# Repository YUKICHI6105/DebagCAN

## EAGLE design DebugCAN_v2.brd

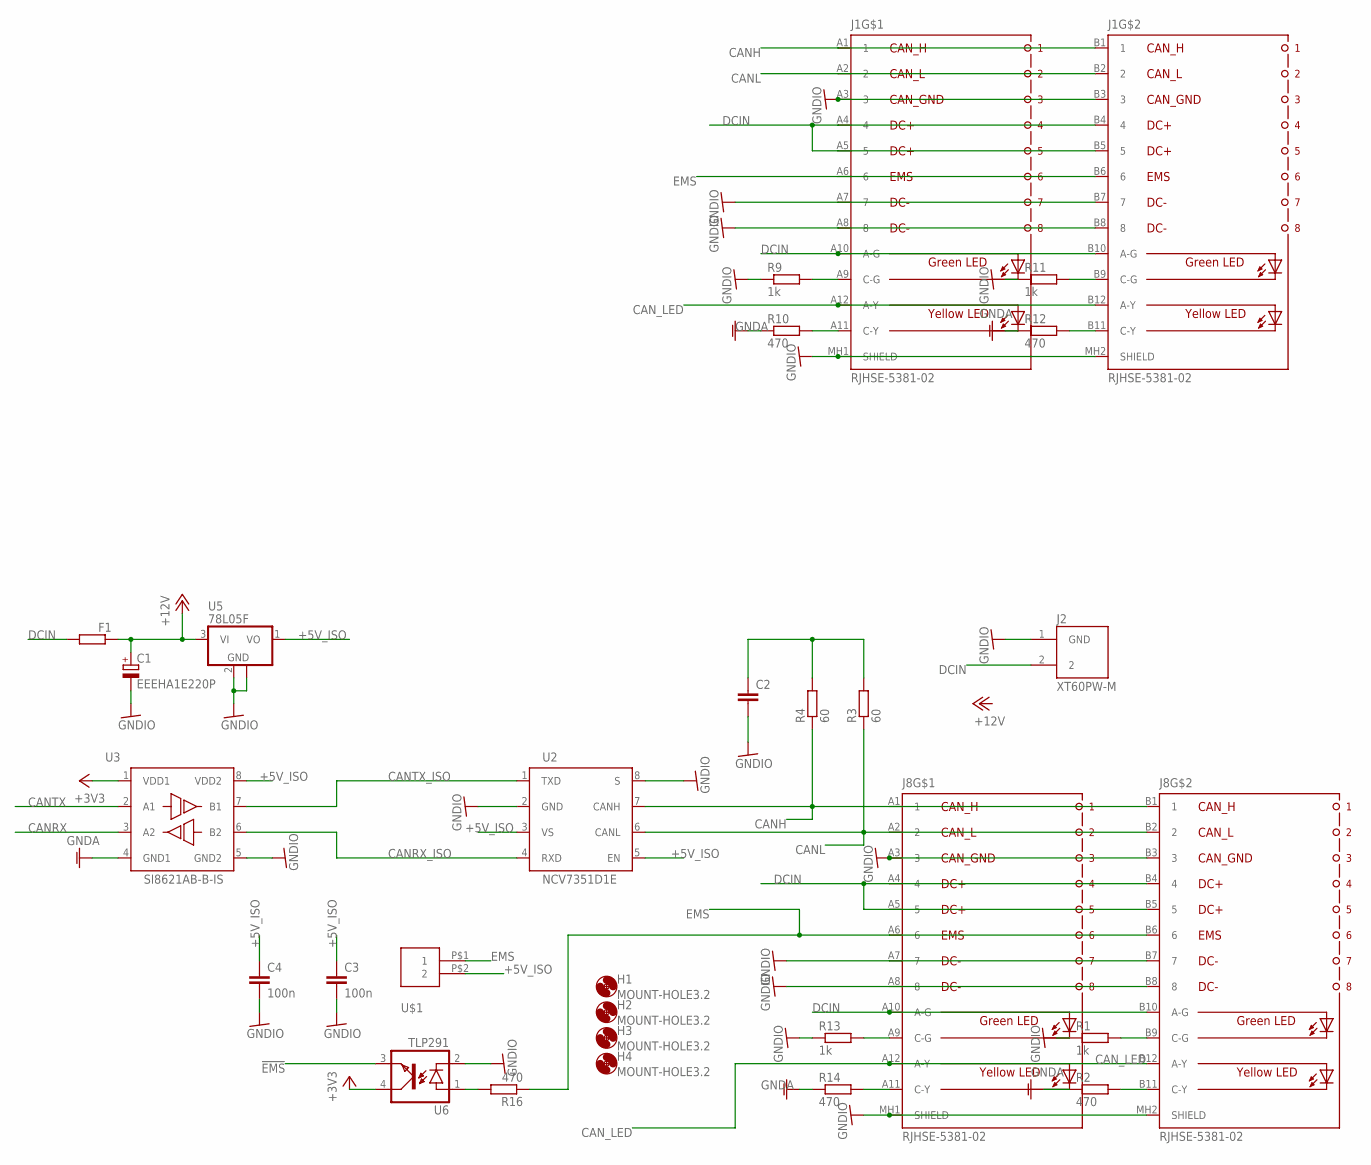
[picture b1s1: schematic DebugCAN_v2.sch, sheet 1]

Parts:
C1: EEEHA1E220P; 153CLV-0605
C2: C-EUC0603; C0603
C3, C4: 100n; C0603
F1: R-EU_R1206; R1206
H1, H2, H3, H4: MOUNT-HOLE3.2; 3,2
J1, J8: RJHSE-5381-02; RJHSE538102
J2: XT60PW-M; AMASS_XT60PW-M
R1, R9, R11, R13: 1k; R0603
R2, R10, R12, R14, R16: 470; R0603
R3, R4: 60; R0603
U2: NCV7351D1E; SO08
U3: SI8621AB-B-IS; SO08
U5: 78L05F; SOT89
U6: TLP291; MINI-FLAT-4
U$1: XH-2-STRAIGHT; CON-XH-2-STRAIGHT

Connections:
!EMS: U6.3 (EMIT); also elsewhere on the board
+3V3: U3.1 (VDD1), U6.4 (COL); also elsewhere on the board
+5V_ISO: C3.1, C4.1, U2.3 (VS), U2.5 (EN), U3.8 (VDD2), U5.1 (VO), U$1.P$2 (2)
+12V: C1.+, F1.1, U5.3 (VI)
CANH: J1.A1 (1), J1.B1 (1), J8.A1 (1), J8.B1 (1), R4.1, U2.7 (CANH)
CANL: J1.A2 (2), J1.B2 (2), J8.A2 (2), J8.B2 (2), R3.1, U2.6 (CANL)
CANRX: U3.3 (A2); also elsewhere on the board
CANRX_ISO: U2.4 (RXD), U3.6 (B2)
CANTX: U3.2 (A1); also elsewhere on the board
CANTX_ISO: U2.1 (TXD), U3.7 (B1)
CAN_LED: J1.A12 (A-Y), J1.B12 (A-Y), J8.A12 (A-Y), J8.B12 (A-Y); also elsewhere on the board
DCIN: F1.2, J1.A4 (4), J1.A5 (5), J1.A10 (A-G), J1.B4 (4), J1.B5 (5), J1.B10 (A-G), J2.2, J8.A4 (4), J8.A5 (5), J8.A10 (A-G), J8.B4 (4), J8.B5 (5), J8.B10 (A-G)
EMS: J1.A6 (6), J1.B6 (6), J8.A6 (6), J8.B6 (6), R16.1, U$1.P$1 (1)
GNDA: R2.1, R10.1, R12.1, R14.1, U3.4 (GND1); also elsewhere on the board
GNDIO: C1.-, C2.2, C3.2, C4.2, J1.A3 (3), J1.A7 (7), J1.A8 (8), J1.B3 (3), J1.B7 (7), J1.B8 (8), J1.MH1 (SHIELD), J1.MH2 (SHIELD), J2.1 (GND), J8.A3 (3), J8.A7 (7), J8.A8 (8), J8.B3 (3), J8.B7 (7), J8.B8 (8), J8.MH1 (SHIELD), J8.MH2 (SHIELD), R1.1, R9.1, R11.1, R13.1, U2.2 (GND), U2.8 (S), U3.5 (GND2), U5.2 (GND), U5.2@1 (GND), U6.2 (C)
unnamed: J1.A9 (C-G), R9.2
unnamed: J8.B9 (C-G), R1.2
unnamed: J8.B11 (C-Y), R2.2
unnamed: C2.1, R3.2, R4.2
unnamed: J1.A11 (C-Y), R10.2
unnamed: J1.B11 (C-Y), R12.2
unnamed: J1.B9 (C-G), R11.2
unnamed: J8.A11 (C-Y), R14.2
unnamed: J8.A9 (C-G), R13.2
unnamed: R16.2, U6.1 (A)

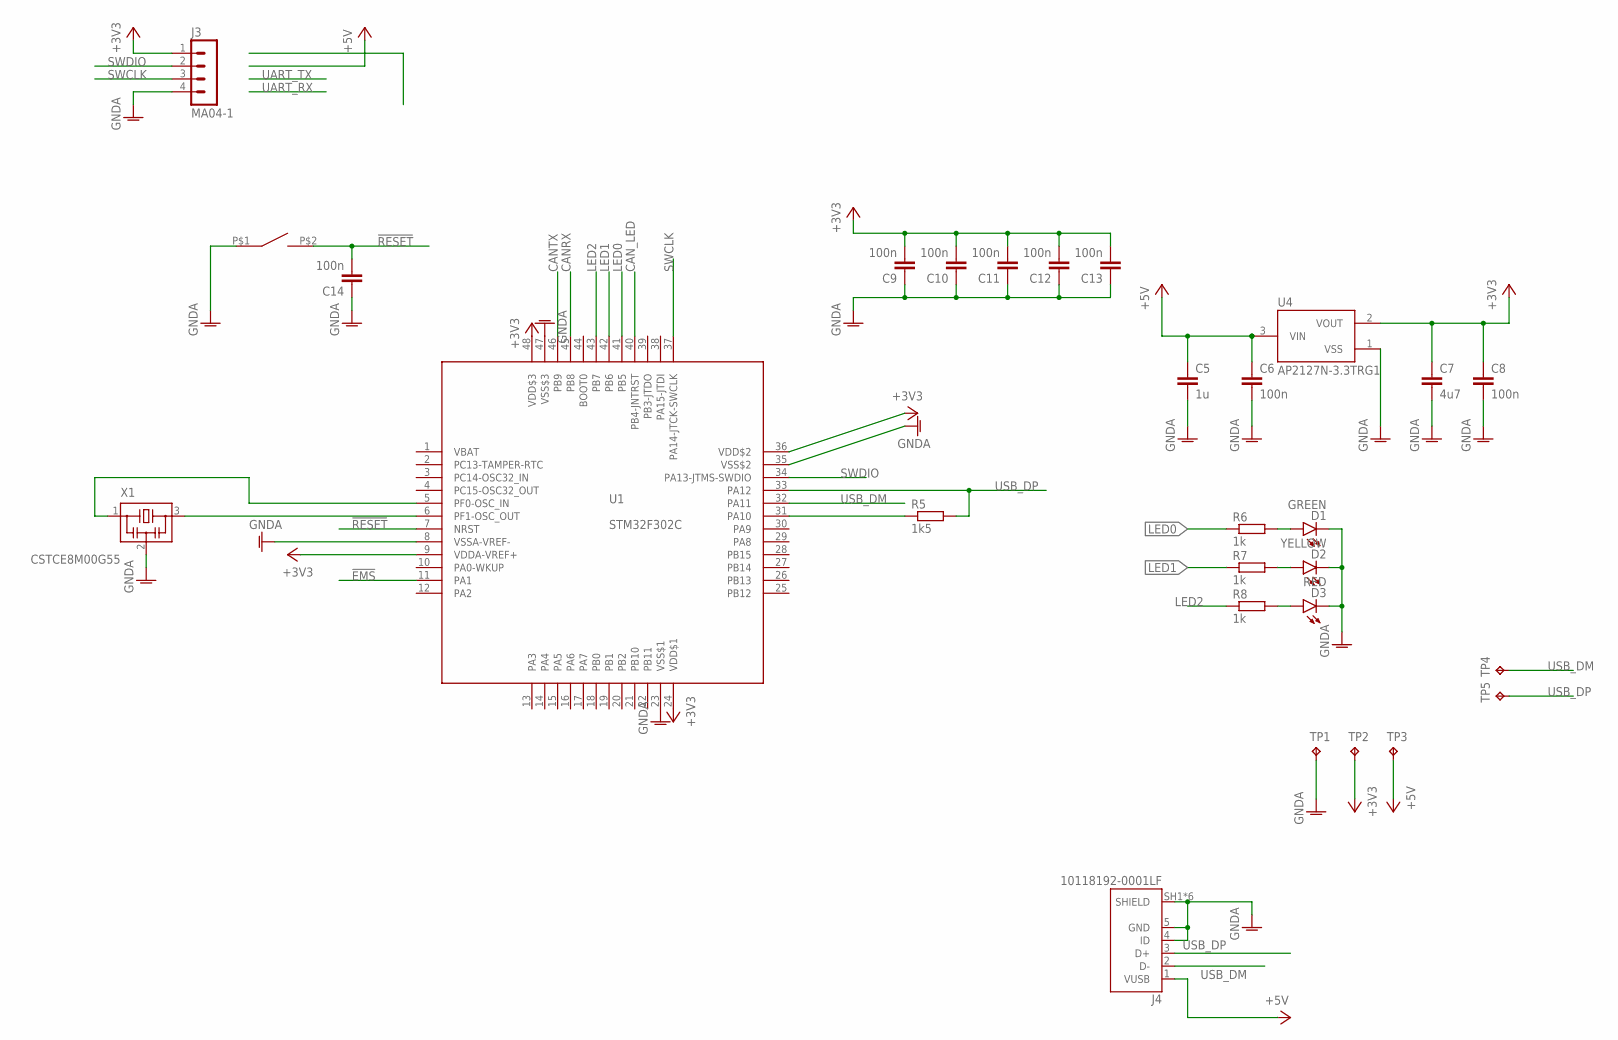
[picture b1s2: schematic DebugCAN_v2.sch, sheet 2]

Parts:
C5: 1u; C0603
C6, C8, C9, C10, C11, C12, C13, C14: 100n; C0603
C7: 4u7; C0805
D1: GREEN; CHIPLED_0805
D2: YELLOW; CHIPLED_0805
D3: RED; CHIPLED_0805
J3: MA04-1
J4: 10118192-0001LF; AMPHENOL_10118192-0001LF
R5: 1k5; R0603
R6, R7, R8: 1k; R0603
S1: SWITCH_TACTILETOP; SWITCH_TACTILE_3X6
TP1, TP2, TP3, TP4, TP5: TPB1,27; B1,27
U1: STM32F302C; LQFP48
U4: AP2127N-3.3TRG1; SOT95P240X110-3
X1: CSTCE8M00G55

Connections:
!EMS: U1.11 (PA1); also elsewhere on the board
!RESET: C14.2, S1.P$2 (2), U1.7 (NRST)
+3V3: C7.1, C8.1, C9.2, C10.2, C11.2, C12.2, C13.2, J3.1, TP2.TP, U1.9 (VDDA-VREF+), U1.24 (VDD$1), U1.36 (VDD$2), U1.48 (VDD$3), U4.2 (VOUT); also elsewhere on the board
+5V: C5.1, C6.1, J4.1 (VUSB), TP3.TP, U4.3 (VIN)
CANRX: U1.45 (PB8); also elsewhere on the board
CANTX: U1.46 (PB9); also elsewhere on the board
CAN_LED: U1.40 (PB4-JNTRST); also elsewhere on the board
GNDA: C5.2, C6.2, C7.2, C8.2, C9.1, C10.1, C11.1, C12.1, C13.1, C14.1, D1.C, D2.C, D3.C, J3.4, J4.4 (ID), J4.5 (GND), J4.SH1 (SHIELD), J4.SH2 (SHIELD), J4.SH3 (SHIELD), J4.SH4 (SHIELD), J4.SH5 (SHIELD), J4.SH6 (SHIELD), S1.P$1 (1), TP1.TP, U1.8 (VSSA-VREF-), U1.23 (VSS$1), U1.35 (VSS$2), U1.47 (VSS$3), U4.1 (VSS), X1.2; also elsewhere on the board
LED0: R6.1, U1.41 (PB5)
LED1: R7.1, U1.42 (PB6)
LED2: R8.1, U1.43 (PB7)
unnamed: D2.A, R7.2
unnamed: D1.A, R6.2
unnamed: U1.6 (PF1-OSC_OUT), X1.3
unnamed: U1.5 (PF0-OSC_IN), X1.1
unnamed: R5.1, U1.31 (PA10)
unnamed: D3.A, R8.2
SWCLK: J3.3, U1.37 (PA14-JTCK-SWCLK)
SWDIO: J3.2, U1.34 (PA13-JTMS-SWDIO)
USB_DM: J4.2 (D-), TP4.TP, U1.32 (PA11)
USB_DP: J4.3 (D+), R5.2, TP5.TP, U1.33 (PA12)

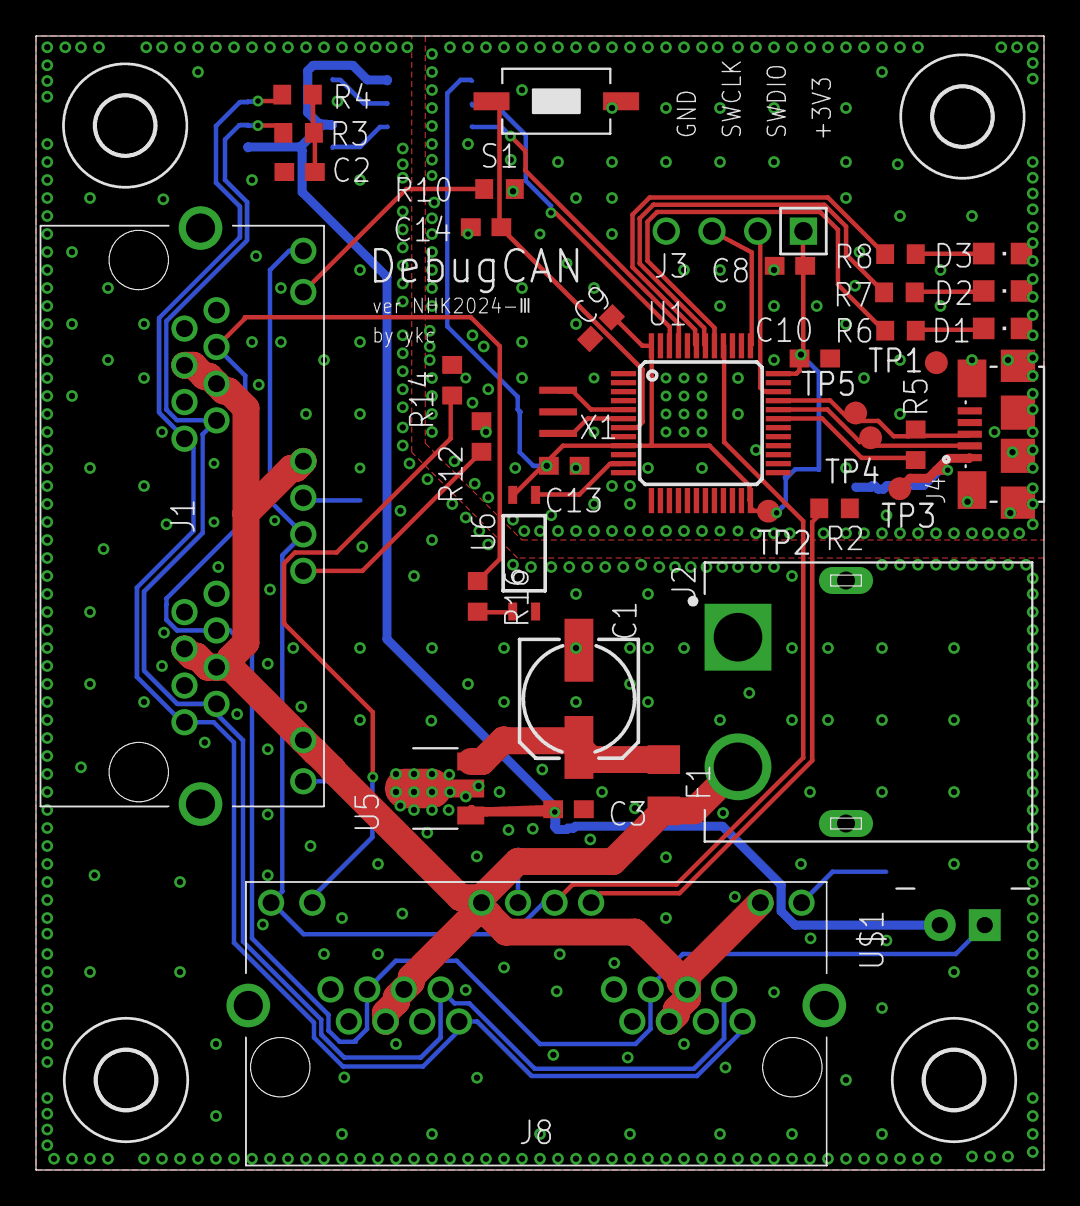
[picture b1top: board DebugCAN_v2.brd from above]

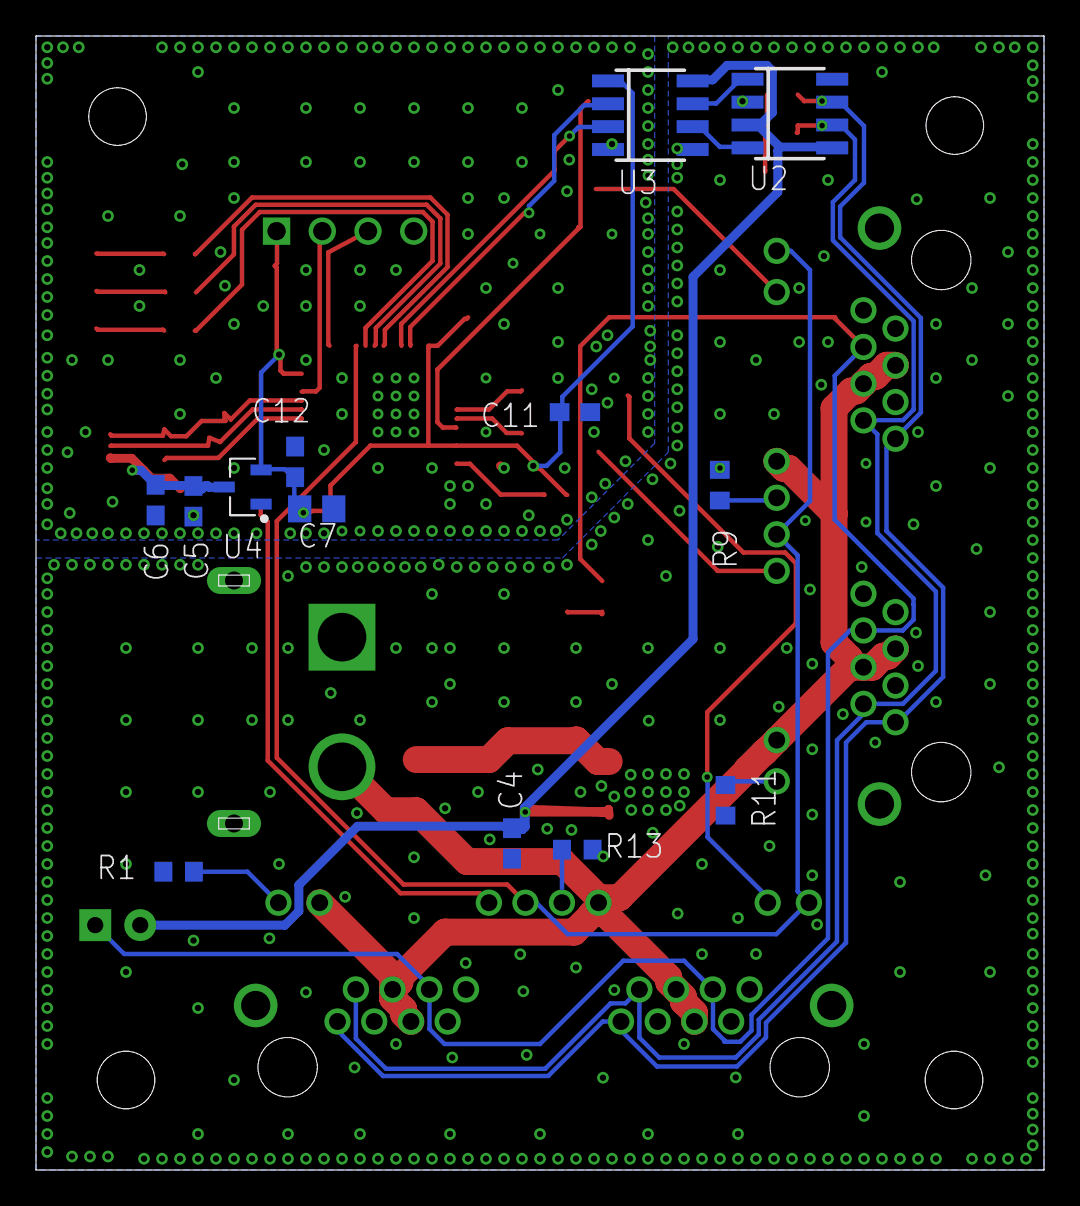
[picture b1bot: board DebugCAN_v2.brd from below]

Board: 2 copper layers, 56.0 x 63.0 mm, 56 parts (13 on the bottom side), 40 nets.

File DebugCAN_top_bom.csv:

Comment,Designator,Footprint,LCSC Part #
1k,C2 R6 R7 R8,R0603,
60,R3 R4,R0603,
78L05F,U5,SOT89,
100n,C3 C9 C10 C13,C0603,
470,R2 R10 R12 R14 R16,R0603,
10118192-0001LF,J4,AMPHENOL_10118192-0001LF,
CSTCE8M00G55,X1,CSTCE8M00G55,
EEEHA1E220P,C1,153CLV-0605,
GREEN,D1,CHIPLED_0805,
NCV7351D1E,U2,SO08,
RED,D3,CHIPLED_0805,
SI8621AB-B-IS,U3,SO08,
STM32F302C,U1,LQFP48,
SWITCH_TACTILETOP,S1,SWITCH_TACTILE_3X6,
TLP291,U6,MINI-FLAT-4,
TPB1 27,TP1,B1 27,
TPB1 27,TP2,B1 27,
TPB1 27,TP3,B1 27,
TPB1 27,TP4,B1 27,
TPB1 27,TP5,B1 27,
YELLOW,D2,CHIPLED_0805,

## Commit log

2023-05-01 設定の同期
2023-05-01 最終調整(シルク)
2023-05-03 USBの変更
2023-05-05 NUC電源の管理を追加
2023-05-12 fainal version
2023-06-03 renew position
2023-06-03 led_regiser_changed
2023-06-05 fainal adjustment
2023-06-05 消すの忘れてた
2023-06-30 シルクの修正
2023-07-01 final update.
2023-08-02 突入電流対策
2023-09-26 change F1
2023-10-16 ver.2 update
